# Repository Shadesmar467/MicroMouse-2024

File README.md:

# MicroMouse 24-25 (IEEE@UCI)
By Adam Wu, Jeremiah Yong, and Jayce Spurgiasz
## Project Summary
A robot(mouse) that navigates a 16x16 cell maze, from corner to center using an STM32F103C8T6(bluepill) microcontroller

**Concepts Utilized:** Floodfill, PWM, Proportional-Integral-Derivative(PID) Correction

**Tools Utilized:** KiCad, STM32CubeIDE, C/C++, soldering, Neovim
## Folder Contents
- Firmware: Code for IR Sensors, motors, encoders, PID, and translation of simulation code to real-world navigation
- Hardware: Kicad layouts and schematics
- Software: Floodfill algorithm, mouse navigation in simulation, and testing

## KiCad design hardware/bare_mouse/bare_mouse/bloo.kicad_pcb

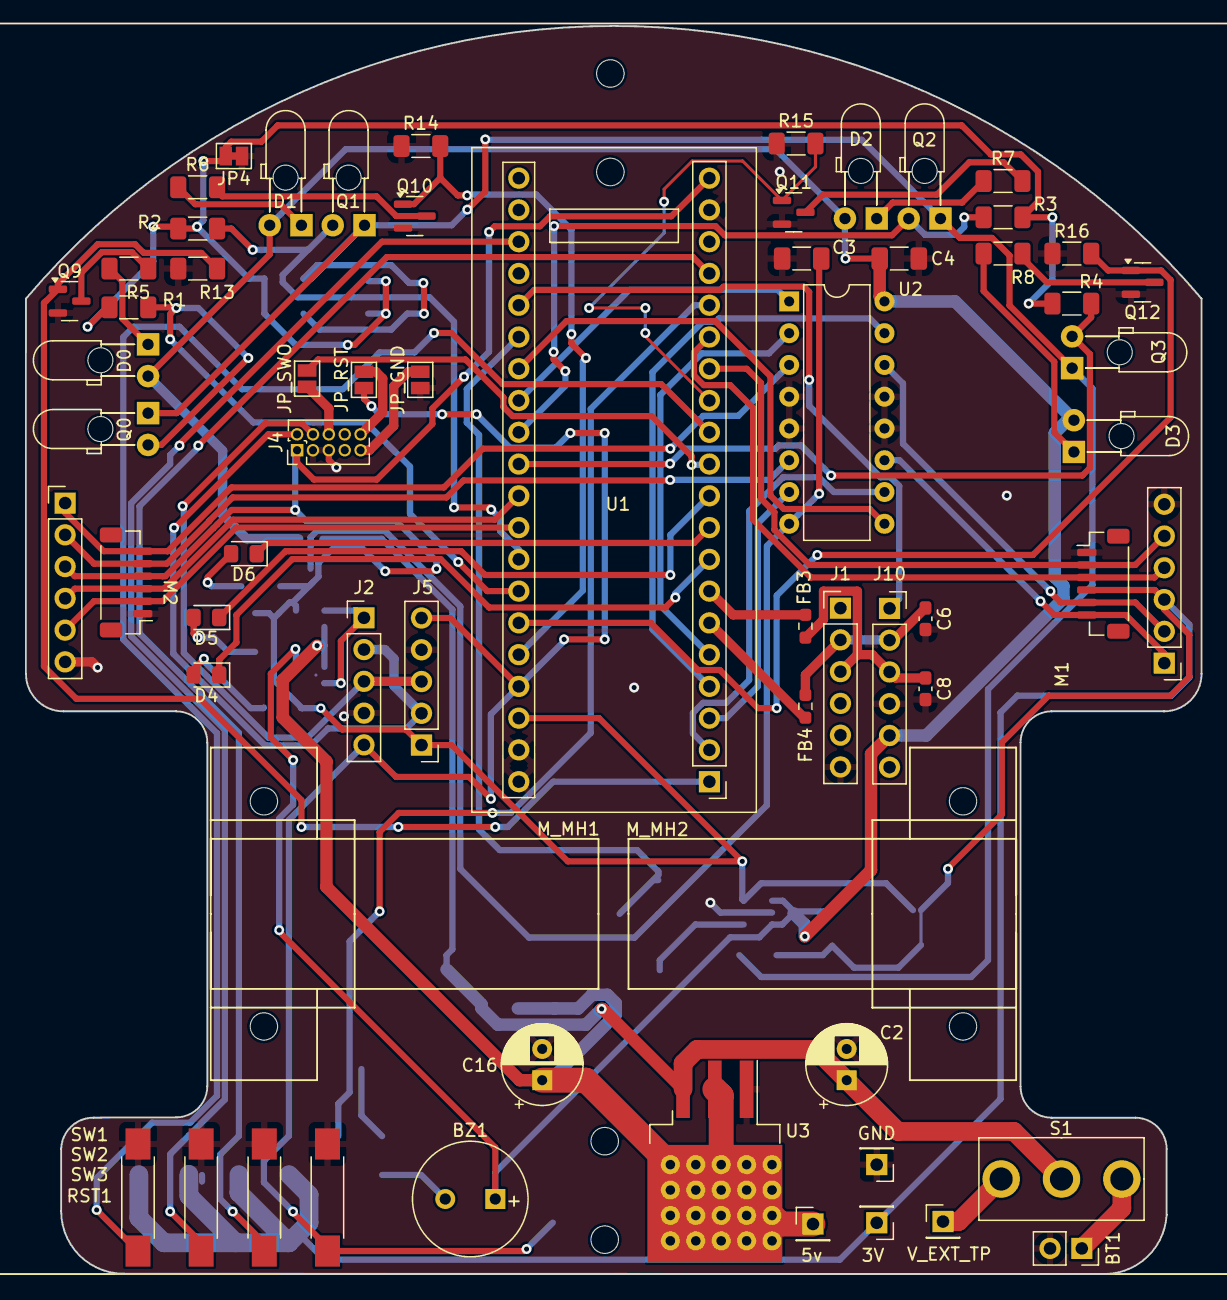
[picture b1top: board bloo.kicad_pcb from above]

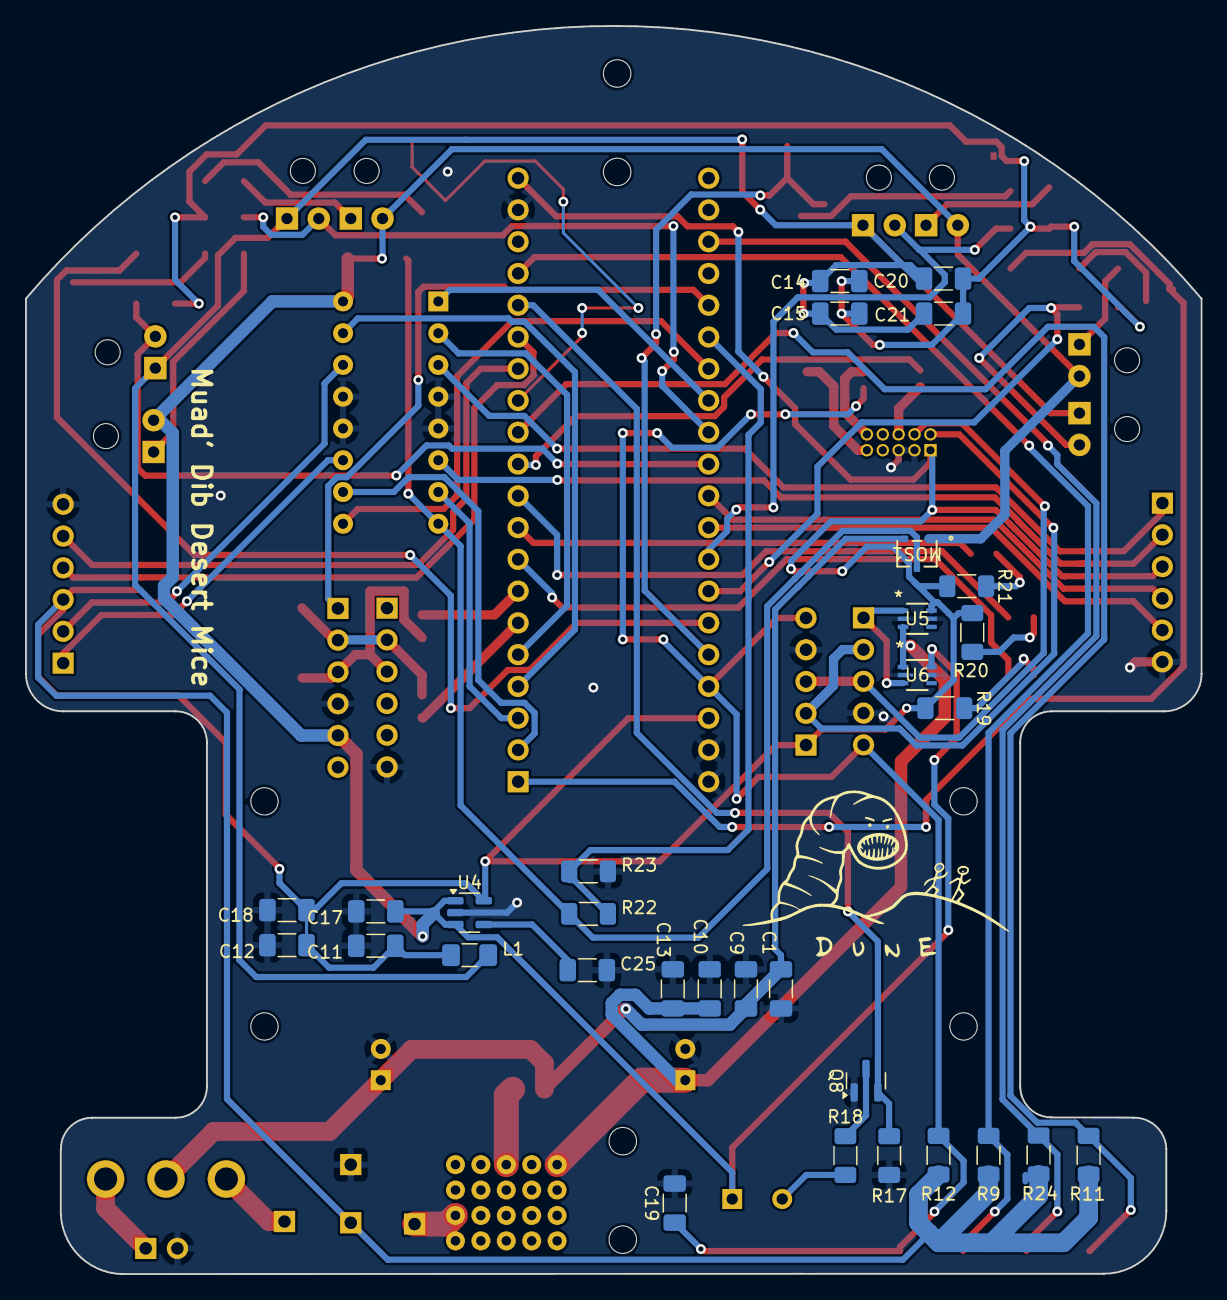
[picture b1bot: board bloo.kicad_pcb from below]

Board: 2 copper layers, 94.0 x 99.8 mm, 97 parts (31 on the bottom side), 67 nets.

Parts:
3V: TP_3V3; PinHeader_1x01_P2.54mm_Vertical
5v: TP_5V; PinHeader_1x01_P2.54mm_Vertical
BT1: Battery_Cell; PinSocket_1x02_P2.54mm_Vertical
BZ1: Buzzer; MagneticBuzzer_PUI_AT-0927-TT-6-R
C1, C4, C12, C13, C19: 0.1uF; C_1206_3216Metric_Pad1.33x1.80mm_HandSolder
C2, C16: 100uF; CP_Radial_D6.3mm_P2.50mm
C3, C14, C15, C17, C18, C20, C21: 1uF; C_1206_3216Metric_Pad1.33x1.80mm_HandSolder
C6, C8: 22pF; C_0603_1608Metric_Pad1.08x0.95mm_HandSolder
C9, C10, C11: 10uF; C_1206_3216Metric_Pad1.33x1.80mm_HandSolder
C25: 10nF; C_1206_3216Metric_Pad1.33x1.80mm_HandSolder
D0, D1, D2, D3: SFH4545; Emitter
D4, D5, D6: LED; LED_0805_2012Metric_Pad1.15x1.40mm_HandSolder
FB3, FB4: HZ0603C601R-10; R_0603_1608Metric_Pad0.98x0.95mm_HandSolder
GND: GND_TP; PinHeader_1x01_P2.54mm_Vertical
J1: Serial Debug Header; PinHeader_1x06_P2.54mm_Vertical
J2, J5: SWD Header; PinHeader_1x05_P2.54mm_Vertical
J4: Conn_ARM_JTAG_SWD_10; PinHeader_2x05_P1.27mm_Vertical
J10: Conn_01x06_Female; PinSocket_1x06_P2.54mm_Vertical
JP4: Jumper_2_Open; SolderJumper-2_P1.3mm_Bridged_Pad1.0x1.5mm
JP_GND: JP_GND; SolderJumper-2_P1.3mm_Open_Pad1.0x1.5mm
JP_RST: JP_RST; SolderJumper-2_P1.3mm_Open_Pad1.0x1.5mm
JP_SWO: JP_SWO; SolderJumper-2_P1.3mm_Open_Pad1.0x1.5mm
L1: 10uH; L_1206_3216Metric_Pad1.42x1.75mm_HandSolder
M1: M1_Conn_Alt; Motor Headers
M2: M2_Conn_Alt; Motor Headers
MOS1: SSM3K335R_LF; SOT-23F_TOS
M_MH1, M_MH2: M2; Motor_mouse
Q0, Q1, Q2, Q3: TEFT4300; Emitter
Q8: Q_NMOS_SGD; SOT-23
Q9, Q10, Q11, Q12: Q_NMOS_GSD; SOT-23
R1, R2, R3, R4: 1.8k; R_1206_3216Metric_Pad1.30x1.75mm_HandSolder
R5, R6, R7, R8: 35; R_1206_3216Metric_Pad1.30x1.75mm_HandSolder
R9, R11, R12, R24: 47K; R_1206_3216Metric_Pad1.30x1.75mm_HandSolder
R13, R14, R15, R16, R17: 47k; R_1206_3216Metric_Pad1.30x1.75mm_HandSolder
R18: 0; R_1206_3216Metric_Pad1.30x1.75mm_HandSolder
R19: 750; R_1206_3216Metric_Pad1.30x1.75mm_HandSolder
R20, R21: 75; R_1206_3216Metric_Pad1.30x1.75mm_HandSolder
R22: 20K; R_1206_3216Metric_Pad1.30x1.75mm_HandSolder
R23: 10K; R_1206_3216Metric_Pad1.30x1.75mm_HandSolder
RST1: SW; SW_SPST_REED_CT05-XXXX-G1
S1: EG1218; MM Switch
SK1, SK2, SK3, SK4: M2; MountingHole_2.2mm_M2
SW1, SW2, SW3: SW; SW_SPST_REED_CT05-XXXX-G1
U1: YAAJ_BluePill_SWD_Breakout; STM32F103
U2: L293D; DIP-16_W7.62mm
U3: LM1085-5.0; 5V Voltage Reg
U4: APE8865Y5-33-HF-3; SOT-23-5
U5, U6: LM66100DCKR; DCK6_TEX
V_EXT_TP: V_EXT_TP; PinHeader_1x01_P2.54mm_Vertical

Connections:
3V3_BYP: C25.1, U4.4 (BYP)
+3.3VA: C14.1, C15.1, C20.1, C21.1, L1.2, Q0.1 (C), Q1.1 (C), Q2.1 (C), Q3.1 (C)
+3V3: 3V.1, C11.1, C12.1, C18.1, J4.1 (VTref), J5.1, L1.1, M1.3, M2.3, R9.1, R11.1, R12.1, R19.2, R20.2, R21.2, R24.1, U1.20 (3V3), U1.38 (3V3), U4.5 (VOUT), U5.6 (VOUT)
+3V3_NET: J2.1, U5.1 (VIN), U6.3 (*CE)
+5V: BZ1.1 (-), C4.1, C17.1, D0.2 (A), D1.2 (A), D2.2 (A), D3.2 (A), J10.5, MOS1.1, U2.16 (VCC1), U4.1 (VIN), U4.3 (~SHDN), U6.6 (VOUT)
+5V_NET: 5v.1, C10.1, C13.1, C16.1, U3.2 (VO), U5.3 (*CE), U6.1 (VIN)
AGND: C14.2, C15.2, C20.2, C21.2, JP4.2 (B), R1.1, R2.1, R3.1, R4.1
BATT_NET: C1.2, C2.1, C9.1, MOS1.2, S1.2, U3.3 (VI)
BLE_STATE: J10.1, U1.25 (PA0)
BUTTON: R11.2, SW1.1, U1.12 (PB4)
BUTTON_2: R24.2, SW2.1, U1.23 (PC14)
BUTTON_3: R9.2, SW3.1, U1.17 (PB9)
BUZZER: Q8.2 (G), R17.2, U1.16 (PB8)
EMIT_1: Q9.1 (G), R13.2, U1.1 (PB12)
EMIT_2: Q10.1 (G), R14.2, U1.36 (PB11)
EMIT_3: Q12.1 (G), R16.2, U1.35 (PB10)
EMIT_4: Q11.1 (G), R15.2, U1.13 (PB5)
GND: BT1.2 (-), C1.1, C2.2, C3.2, C4.2, C6.2, C8.2, C9.2, C10.2, C11.2, C12.2, C13.2, C16.2, C17.2, C18.2, C19.2, C25.2, GND.1, J1.6, J2.4, J4.3 (GND), J4.5 (GND), J5.4, J10.4, JP4.1 (A), JP_GND.1 (A), M1.6, M2.6, Q8.1 (S), Q9.2 (S), Q10.2 (S), Q11.2 (S), Q12.2 (S), R13.1, R14.1, R15.1, R16.1, R17.1, R23.2, RST1.2, SW1.2, SW2.2, SW3.2, U1.19 (GND), U1.39 (GND), U1.40 (GND), U2.4 (GND), U2.5 (GND), U2.12 (GND), U2.13 (GND), U3.1 (GND), U4.2 (GND), U5.2 (GND), U5.5 (ST), U6.2 (GND), U6.5 (ST)
LED_BLUE: D6.1 (K), U1.9 (PA12)
LED_GREEN: D5.1 (K), U1.10 (PA15)
LED_RED: D4.1 (K), U1.8 (PA11)
M1_BACK: U1.3 (PB14), U2.7 (2A)
M1_ENC_A: M2.4, U1.31 (PA6)
M1_ENC_B: M2.5, U1.32 (PA7)
M1_FWD: U1.5 (PA8), U2.2 (1A)
M1_OUT_1: M2.1, U2.3 (1Y)
M1_OUT_2: M2.2, U2.6 (2Y)
M1_SPD: U1.28 (PA3), U2.1 (EN1,2)
M2_BACK: U1.4 (PB15), U2.15 (4A)
M2_ENC_A: M1.4, U1.15 (PB7)
M2_ENC_B: M1.5, U1.14 (PB6)
M2_FWD: U1.2 (PB13), U2.10 (3A)
M2_OUT_1: M1.1, U2.11 (3Y)
M2_OUT_2: M1.2, U2.14 (4Y)
M2_SPD: U1.27 (PA2), U2.9 (EN3,4)
unnamed: BT1.1 (+), S1.1
unnamed: BZ1.2 (+), R18.2
unnamed: D0.1 (K), R5.1
unnamed: D1.1 (K), R6.1
unnamed: D2.1 (K), R7.1
unnamed: D3.1 (K), R8.1
unnamed: D4.2 (A), R19.1
unnamed: D5.2 (A), R20.1
unnamed: D6.2 (A), R21.1
unnamed: C6.1, FB4.1, J1.2, J10.2
unnamed: C8.1, FB3.2, J1.3, J10.3
unnamed: J4.9 (GNDDetect), JP_GND.2 (B)
unnamed: J4.6 (SWO/TDO), JP_SWO.1 (A)
unnamed: J4.10 (~RESET), JP_RST.2 (B)
unnamed: Q8.3 (D), R18.1
unnamed: Q9.3 (D), R5.2
unnamed: Q10.3 (D), R6.2
unnamed: Q11.3 (D), R7.2
unnamed: Q12.3 (D), R8.2
unnamed: S1.3, V_EXT_TP.1
RECEIV_1: Q0.2 (E), R1.2, U1.34 (PB1)
RECEIV_2: Q1.2 (E), R2.2, U1.33 (PB0)
RECEIV_3: Q3.2 (E), R4.2, U1.30 (PA5)
RECEIV_4: Q2.2 (E), R3.2, U1.29 (PA4)
RST: C19.1, J2.5, J5.5, JP_RST.1 (A), R12.2, RST1.1, U1.37 (RST)
SWDCLK: J2.3, J4.4 (SWDCLK/TCK), J5.3
SWDIO: J2.2, J4.2 (SWDIO/TMS), J5.2
SWO: JP_SWO.2 (B), U1.11 (PB3)
USART1_RX: FB3.1, U1.7 (PA10)
USART1_TX: FB4.2, U1.6 (PA9)
VCC: C3.1, MOS1.3, R22.1, U2.8 (VCC2)
V_METER: R22.2, R23.1, U1.26 (PA1)

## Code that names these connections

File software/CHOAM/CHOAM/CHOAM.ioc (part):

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Mcu.Name=STM32F103C(8-B)Tx
Mcu.Package=LQFP48
Mcu.UserName=STM32F103C8Tx
PA0-WKUP.GPIOParameters=GPIO_Label
PA0-WKUP.GPIO_Label=BLE_STATE
PA0-WKUP.Signal=GPIO_Output
PA1.Signal=ADCx_IN1
PA10.Signal=USART1_RX
PA11.GPIOParameters=GPIO_Label
PA11.GPIO_Label=LED_RED
PA11.Signal=GPIO_Output
PA12.GPIOParameters=GPIO_Label
PA12.GPIO_Label=LED_BLUE
PA12.Signal=GPIO_Output
PA13.Mode=Serial_Wire
PA13.Signal=SYS_JTMS-SWDIO
PA14.Mode=Serial_Wire
PA14.Signal=SYS_JTCK-SWCLK
PA15.GPIOParameters=GPIO_Label
PA15.GPIO_Label=LED_GREEN
PA15.Signal=GPIO_Output
PA2.GPIOParameters=GPIO_Label
PA2.GPIO_Label=MR_PWM
PA2.Signal=S_TIM2_CH3
PA3.GPIOParameters=GPIO_Label
PA3.GPIO_Label=ML_PWM
PA3.Signal=S_TIM2_CH4
PA4.GPIOParameters=GPIO_Label
PA4.GPIO_Label=REC_FR
PA4.Signal=ADCx_IN4
PA5.GPIOParameters=GPIO_Label
PA5.GPIO_Label=REC_SR
PA5.Signal=ADCx_IN5
PA6.GPIOParameters=GPIO_Label
PA6.GPIO_Label=ML_ENC_A
PA6.Signal=S_TIM3_CH1
PA7.GPIOParameters=GPIO_Label
PA7.GPIO_Label=ML_ENC_B
PA7.Signal=S_TIM3_CH2
PA8.GPIOParameters=GPIO_Label
PA8.GPIO_Label=ML_FWD
PA8.Signal=GPIO_Output
PA9.Signal=USART1_TX
PB0.GPIOParameters=GPIO_Label
PB0.GPIO_Label=REC_FL
PB0.Signal=ADCx_IN8
PB1.GPIOParameters=GPIO_Label
PB1.GPIO_Label=REC_SL
PB1.Signal=ADCx_IN9
PB10.GPIOParameters=GPIO_Label
PB10.GPIO_Label=EMIT_SR
PB10.Signal=GPIO_Output
PB11.GPIOParameters=GPIO_Label
PB11.GPIO_Label=EMIT_FL
PB11.Signal=GPIO_Output
PB12.GPIOParameters=GPIO_Label
PB12.GPIO_Label=EMIT_SL
PB12.Signal=GPIO_Output
PB13.GPIOParameters=GPIO_Label
PB13.GPIO_Label=MR_FWD
PB13.Signal=GPIO_Output
PB14.GPIOParameters=GPIO_Label
PB14.GPIO_Label=ML_BWD
PB14.Signal=GPIO_Output
PB15.GPIOParameters=GPIO_Label
PB15.GPIO_Label=MR_BWD
PB15.Signal=GPIO_Output
PB3.GPIOParameters=GPIO_Label
PB3.GPIO_Label=SWO
PB3.Signal=GPIO_Output
PB4.Signal=GPIO_Input
PB5.GPIOParameters=GPIO_Label
PB5.GPIO_Label=EMIT_FR
PB5.Signal=GPIO_Output
PB6.GPIOParameters=GPIO_Label
PB6.GPIO_Label=MR_ENC_B
PB6.Signal=S_TIM4_CH1
PB7.GPIOParameters=GPIO_Label
PB7.GPIO_Label=MR_ENC_A
PB7.Signal=S_TIM4_CH2
PB8.GPIOParameters=GPIO_Label
PB8.GPIO_Label=BUZZER
PB8.Signal=GPIO_Output
PC13-TAMPER-RTC.Signal=GPIO_Output
PC14-OSC32_IN.Signal=GPIO_Input
PD0-OSC_IN.Mode=HSE-External-Oscillator
PD0-OSC_IN.Signal=RCC_OSC_IN
PD1-OSC_OUT.Mode=HSE-External-Oscillator
PD1-OSC_OUT.Signal=RCC_OSC_OUT
RCC.SYSCLKFreq_VALUE=72000000
RCC.SYSCLKSource=RCC_SYSCLKSOURCE_PLLCLK
board=custom

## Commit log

2024-10-31 direction, position, walls, goal, complete
2024-11-08 getNeighborCells function complete!
2024-11-10 floodfill done
2024-11-14 current progres
2024-11-14 floodfill inner for loop works
2024-11-14 fix floodfill to work for empty maze
2024-11-14 fix log messages to be more clear
2024-11-14 walls work
2024-11-14 initial getBestCell implementation
2024-11-14 functioning getBestCell() but neighborCell() edge case isnt working
2024-11-14 fixed neighborCell() to not give cells blocked by walls
2024-11-14 move function finished, no more left hand turn
2024-11-14 attempting to fix floodfill, doesnt account for walls currently
2024-11-14 move works, floodfill still broken. Intialization works
2024-11-14 fix maze initialization
2024-11-14 working on floodfill, not complete
2024-11-14 best version of floodfill, not accounting for walls yet
2024-11-16 not working yet
2024-11-16 Voice from the Outer World
2024-11-19 read me
2024-11-19 read me v2
2024-11-19 create software folder
2024-11-19 reorganized files into software folder
2024-11-19 reorganized all software files into software folder
2024-11-19 initial commit creating hardware file
2024-11-20 commenting and cleaning up redundant code
2024-11-21 kicad files added
2024-11-26 initial commit, starting adams pcb
2024-11-26 place footprints and begin routing power section
2024-11-26 same as previous
2024-11-26 checkin changes
2024-11-26 fixing mac windows differences
2024-11-28 jeremiah PCB
2024-11-29 merged adam PCB into master
2024-11-29 LED & switch wiring, mouse lost weight
2024-11-29 recommitting jeremiah's changes
2024-11-29 remote repository up to date, yongi replaces master
2024-11-29 initial commit for motor driver and bottom right schematic
2024-11-30 power ORing, SWD header, and other adam sections traced
2024-11-30 wiring done
2024-11-30 wiring done for real
2024-12-02 connections complete
2024-12-02 resolved outlines issue and added some vias to fix grounding planes
2024-12-02 oopsies didnt save last time
2024-12-05 changes after meeting with eaton
2024-12-05 errors resolved. JP4 too far away from capacitors?
2024-12-06 added most important part
2024-12-15 added team names to back silkscreen
2024-12-15 created zip file for submission
2024-12-30 Update README.md in software
2025-01-12 deadEndCheck in progress
2025-01-13 zip file for pcb
2025-01-13 add gitignore for kicad metadata files
2025-01-14 add comments and changed structure of deadEndCheck
2025-01-14 dead end complete
2025-01-15 move readme to main folder and remove red square highlighting
2025-01-21 i might have added the stm32 files to the repo
2025-02-28 CHOAM initial push
2025-03-01 configure emitter pins
2025-03-02 distance and adc_manager modules as well as .gitignore
2025-03-02 removed .metadata files and changed .gitignore
2025-03-02 added comment
2025-03-05 solved some errors, created more
2025-03-12 board blew up
2025-03-27 fixed STLINK (I think), updated code with support for all IR sensors
2025-03-29 added motors .c/.h, initialized PWM start
2025-04-02 changed motors, made commenct and small changes
2025-04-04 encoders recording, need to be converted to distance. motors nonfunctional, code seems correct. IR sensors not recording, causes 'target not found, retrying' message to appear. changed motors.c, remo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
2025-04-06 adam work on motors and encoders
2025-04-09 motors working
2025-04-10 work on IR sensors
2025-04-11 add setGoalPos functionality, mouse can go to any position
2025-04-21 working ir sensors
2025-04-21 fix nested choam directories
2025-04-23 please linker be in here somehwere
2025-04-25 working mouse, new movement.c file
2025-04-26 rough turn functions created (they work based on the assumption that the current encoder calibration is correct)
2025-04-30 overflow accounted for
2025-04-30 think updated .gitignore to stop tracking metadata
2025-04-30 gitignore updated for stm metadata
2025-04-30 .gitignore updated to exclude firmware metadata
2025-04-30 straight driving and front wall straightening
2025-05-01 fine tuning move_dist()
2025-05-07 move_dist pretty straight now
2025-05-07 floodfill files improved, reorganized, in stm32cubeide
2025-05-07 removed all unecessary API calls in floodFill, replaced with correct code
2025-05-08 cleaned up distance.c
2025-05-08 update .gitignore with firmware/.metadata/
2025-05-08 idk whats happening
2025-05-08 .gitignore change
2025-05-08 getting rid of .metadata files
2025-05-08 getting rid of .metadata files again
2025-05-08 getting rid of .metadata files finally, hopefully
2025-05-08 getting rid of .metadata inside firmware
2025-05-08 getting rid of .metadata inside .vscode
2025-05-08 FIXED AIOJFORIEJGOIJ
2025-05-09 add floodFill to build, fixed errors
2025-05-10 caveman wall detection front
2025-05-10 stop constants updated for jeremiah's bedroom
2025-05-13 Wrote front_straighten, needs calibration and testing
2025-05-14 included a thing
2025-05-14 broken walldetection
2025-05-15 fixed 17 errors, SCALE values no work
2025-05-16 fixed SCALE values to use floating point division
2025-05-16 add walldetect to move_dist
2025-05-16 improvements to pid
2025-05-16 workable pid version
2025-05-18 finished pid and walldetect functions
2025-05-18 create header files
2025-05-18 create floodfill c folder
2025-05-18 afgiufeohqrwhougisfhwoieurhgoeriuhgohe
2025-05-18 please let this be light
2025-05-18 formatted code, added comments
2025-05-18 integration def working firs try
2025-05-19 floodfill files commented, formatted, and fixed
2025-05-19 more formatting
2025-05-20 floodfill integration work
2025-05-20 troubleshooting pid
2025-05-20 floodfill integrated with PID & movement, pretty bad tho
2025-05-21 jeremiah laptop blew up
2025-05-21 calbratio
2025-05-21 working mouse
2025-05-22 updating
2025-05-22 added separate values for differing pids
2025-05-22 flipped logic of one wall pid
2025-05-22 rework/revise jayce code, mouse is drunk
2025-05-23 encoder PID created, not tuned. code cleaned
2025-05-25 working on pid
2025-05-25 working on pid more
2025-05-25 encoder PID updated to account for turns
2025-05-25 broken mouse
2025-05-25 ir values for aamc maze
